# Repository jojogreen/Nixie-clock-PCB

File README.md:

# Nixie-clock-PCB

Added the repository
Nixie Clock PCB

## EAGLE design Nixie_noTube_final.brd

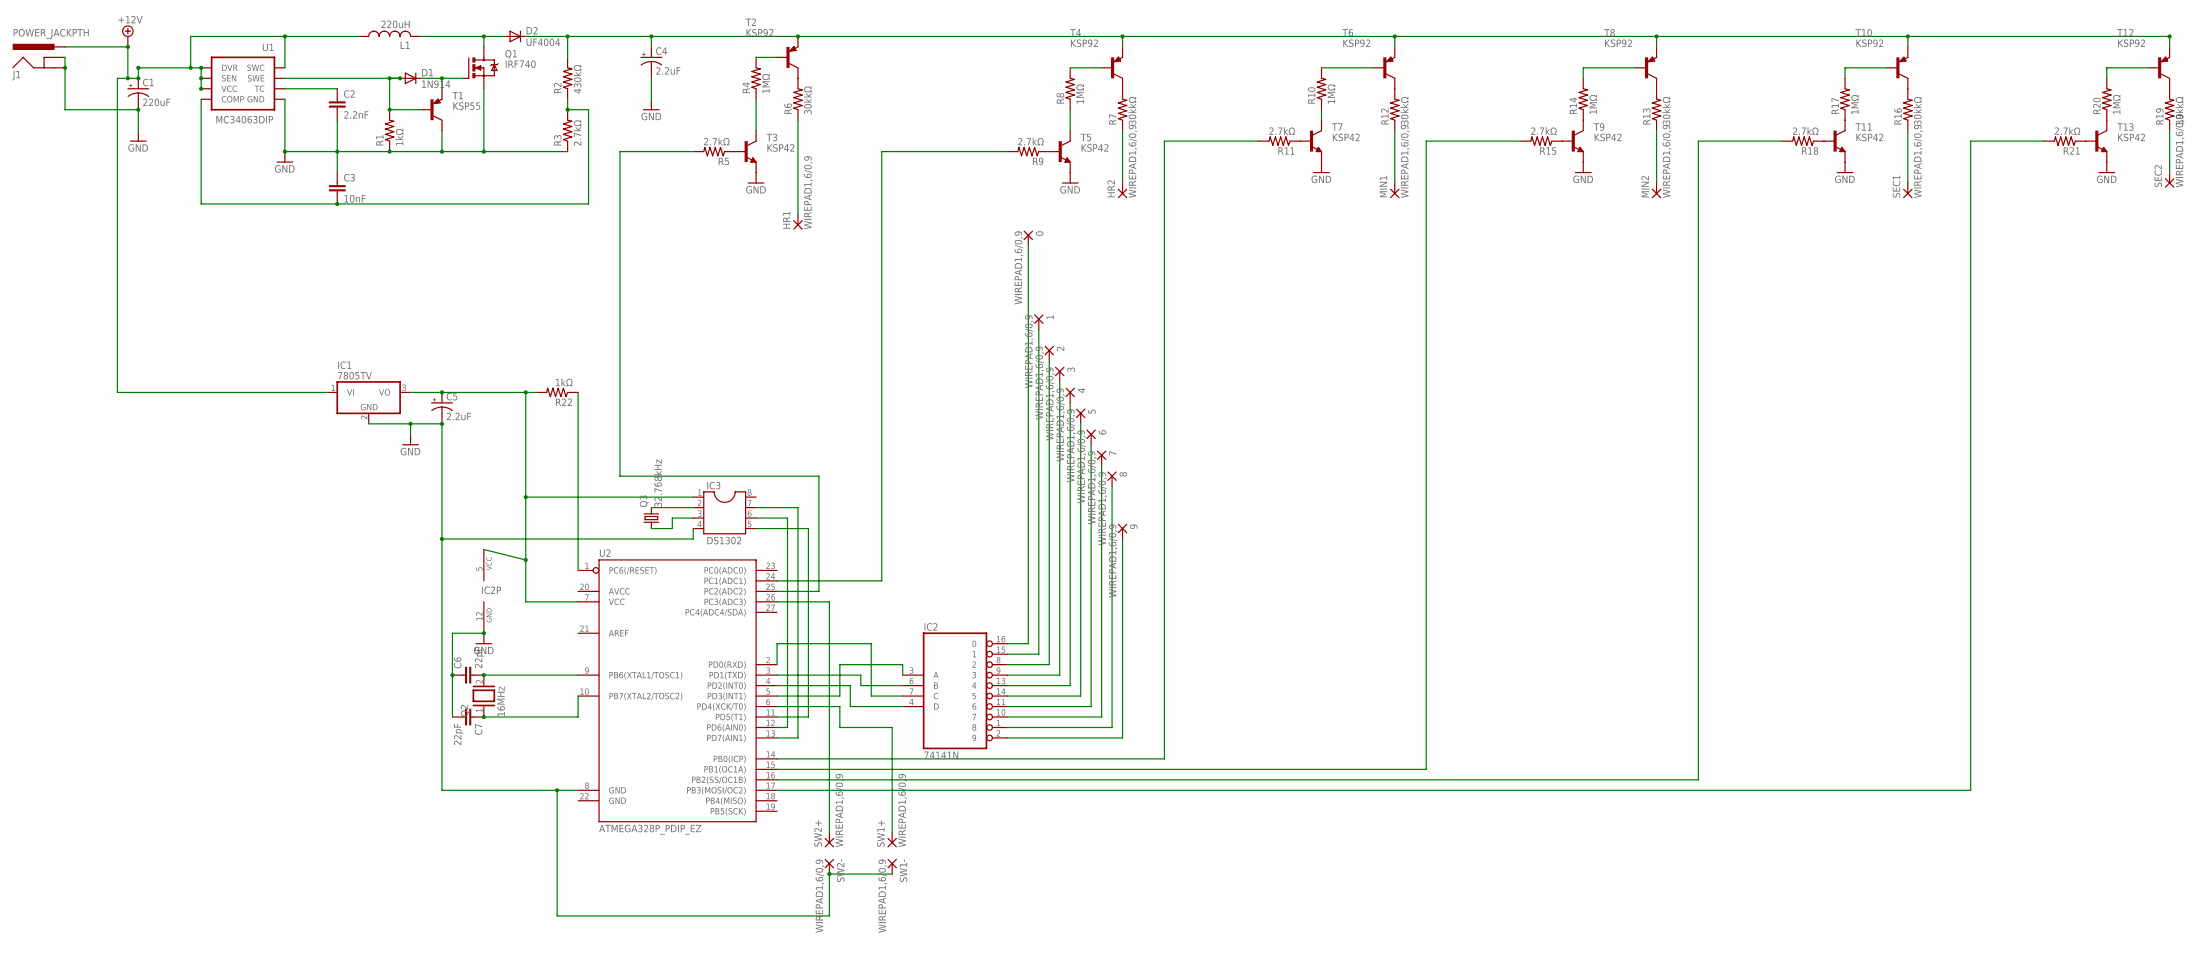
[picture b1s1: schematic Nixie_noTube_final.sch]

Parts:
0, 1, 2, 3, 4, 5, 6, 7, 8, 9: WIREPAD1,6/0,9; 1,6/0,9
C1: 220uF; CPOL-RADIAL-100UF-25V
C2: 2.2nF; CAP-PTH-SMALLEZ
C3: 10nF; CAP-PTH-SMALLEZ
C4, C5: 2.2uF; CPOL-RADIAL-100UF-25V
C6, C7: 22pF; C2.5-3
D1: 1N914; DO41-10
D2: UF4004; DO41-10
HR1, HR2: WIREPAD1,6/0,9; 1,6/0,9
IC1: 7805TV; TO220V
IC2: 74141N; DIL16
IC3: DS1302; DIL08
J1: POWER_JACKPTH; POWER_JACK_PTH
L1: 220uH; 6000-XXXX-RC
MIN1, MIN2: WIREPAD1,6/0,9; 1,6/0,9
Q1: IRF740; TO220BV
Q2: 16MHz; QS
Q3: 32.768kHz; TC26H
R1, R22: 1kΩ; 0204/7
R2: 430kΩ; 0204/7
R3, R5, R9, R11, R15, R18, R21: 2.7kΩ; 0204/7
R4, R8, R10, R14, R17, R20: 1MΩ; 0204/7
R6, R7, R12, R13, R16, R19: 30kkΩ; 0204/7
SEC1, SEC2: WIREPAD1,6/0,9; 1,6/0,9
SW1+, SW1-, SW2+, SW2-: WIREPAD1,6/0,9; 1,6/0,9
T1: KSP55; TO92-EBC
T2, T4, T6, T8, T10, T12: KSP92; TO92
T3, T5, T7, T9, T11, T13: KSP42; TO92
U1: MC34063DIP; DIP-08
U2: ATMEGA328P_PDIP_EZ; DIL28-EZ

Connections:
200V: C4.1 (+), D2.C, R2.2, T2.1 (E), T4.1 (E), T6.1 (E), T8.1 (E), T10.1 (E), T12.1 (E)
+12V: C1.1 (+), IC1.1 (VI), J1.PWR, L1.1, U1.1 (SWC), U1.6 (VCC), U1.7 (SEN), U1.8 (DVR)
GND: C1.2 (-), C2.2, C3.1, C4.2 (-), C5.2 (-), C6.1, C7.2, IC1.2 (GND), IC2.12 (GND), IC3.4, J1.GND, J1.GNDBREAK, Q1.S, R1.1, R3.1, SW1-.1, SW2-.1, T1.C, T3.1 (E), T5.1 (E), T7.1 (E), T9.1 (E), T11.1 (E), T13.1 (E), U1.4 (GND), U2.8 (GND)
H1: HR2.1, R7.1
unnamed: C2.1, U1.3 (TC)
unnamed: C3.2, R2.1, R3.2, U1.5 (COMP)
unnamed: D1.A, R1.2, T1.B, U1.2 (SWE)
unnamed: D1.C, Q1.G, T1.E
unnamed: D2.A, L1.2, Q1.D
unnamed: R19.1, SEC2.1
unnamed: R11.1, T7.2 (B)
unnamed: R6.2, T2.3 (C)
unnamed: R4.2, T2.2 (B)
unnamed: R4.1, T3.3 (C)
unnamed: R5.1, T3.2 (B)
unnamed: HR1.1, R6.1
unnamed: R7.2, T4.3 (C)
unnamed: R9.1, T5.2 (B)
unnamed: R8.2, T4.2 (B)
unnamed: R8.1, T5.3 (C)
unnamed: R12.2, T6.3 (C)
unnamed: R10.1, T7.3 (C)
unnamed: MIN1.1, R12.1
unnamed: R10.2, T6.2 (B)
unnamed: R13.2, T8.3 (C)
unnamed: R14.1, T9.3 (C)
unnamed: R15.1, T9.2 (B)
unnamed: R14.2, T8.2 (B)
unnamed: MIN2.1, R13.1
unnamed: R16.2, T10.3 (C)
unnamed: R17.1, T11.3 (C)
unnamed: R18.1, T11.2 (B)
unnamed: R17.2, T10.2 (B)
unnamed: R16.1, SEC1.1
unnamed: R19.2, T12.3 (C)
unnamed: R20.1, T13.3 (C)
unnamed: R21.1, T13.2 (B)
unnamed: R20.2, T12.2 (B)
unnamed: R22.1, U2.1 (PC6(/RESET))
unnamed: C5.1 (+), IC1.3 (VO), IC2.5 (VCC), IC3.1, R22.2, U2.7 (VCC)
unnamed: IC2.6 (B), U2.3 (PD1(TXD))
unnamed: C6.2, Q2.2, U2.9 (PB6(XTAL1/TOSC1))
unnamed: C7.1, Q2.1, U2.10 (PB7(XTAL2/TOSC2))
unnamed: IC2.7 (C), U2.2 (PD0(RXD))
unnamed: IC2.4 (D), U2.4 (PD2(INT0))
unnamed: IC2.3 (A), U2.5 (PD3(INT1))
unnamed: 0.1, IC2.16 (0)
unnamed: 1.1, IC2.15 (1)
unnamed: 2.1, IC2.8 (2)
unnamed: 3.1, IC2.9 (3)
unnamed: 4.1, IC2.13 (4)
unnamed: 5.1, IC2.14 (5)
unnamed: 6.1, IC2.11 (6)
unnamed: 7.1, IC2.10 (7)
unnamed: 8.1, IC2.1 (8)
unnamed: 9.1, IC2.2 (9)
unnamed: SW1+.1, U2.6 (PD4(XCK/T0))
unnamed: SW2+.1, U2.26 (PC3(ADC3))
unnamed: R5.2, U2.25 (PC2(ADC2))
unnamed: R9.2, U2.24 (PC1(ADC1))
unnamed: R11.2, U2.14 (PB0(ICP))
unnamed: R15.2, U2.15 (PB1(OC1A))
unnamed: R18.2, U2.16 (PB2(SS/OC1B))
unnamed: R21.2, U2.17 (PB3(MOSI/OC2))
unnamed: IC3.2, Q3.2
unnamed: IC3.3, Q3.1
unnamed: IC3.5, U2.11 (PD5(T1))
unnamed: IC3.6, U2.12 (PD6(AIN0))
unnamed: IC3.7, U2.13 (PD7(AIN1))

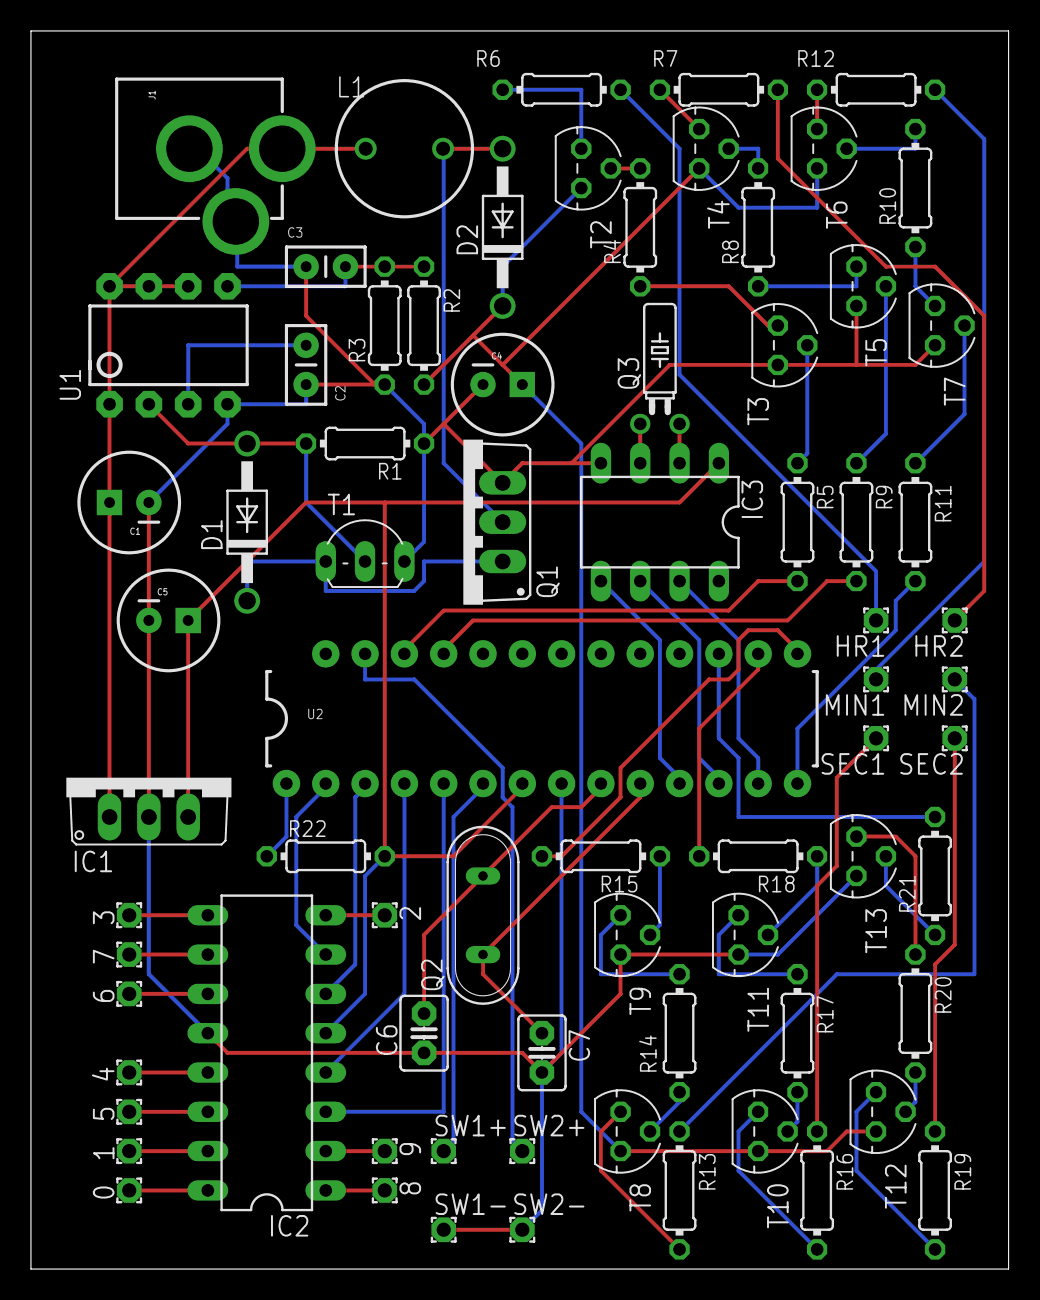
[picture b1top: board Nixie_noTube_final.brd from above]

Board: 2 copper layers, 63.2 x 80.0 mm, 74 parts (0 on the bottom side), 69 nets.

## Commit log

2016-08-30 Added eagle files & .png of pics
2016-09-09 Added revision 2
    rev 2 includes DS1307 instead of DS1302, changes some pins, and makes board a little bigger

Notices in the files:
parts and their libraries:
SparkFun-Capacitors: Licensing: Creative Commons ShareAlike 4.0 International - https://creativecommons.org/licenses/by-sa/4.0
